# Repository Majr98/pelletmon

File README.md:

# WHAT AND WHY?

Our old boiler was previously connected to my IoT system. After replacing the boiler with a new one, we no longer have this option. So why not introduce it to a new boiler?

# THE TARGET

The goal of the project is to reverse engineer the CAN communication of the new boiler and expose real-time data to the IoT. By the way, the HC-SR04 sensor will measure the fuel level in the tank.

# DESIGN

The project will have its own PCB. Communication with the outside world will be carried out using ESP32 and fuel level measurement using HC-SR04. The SN65HVD230 chip will be used as the CAN transceiver. The software will be written in the Arduino environment in C ++ and will be powered with my IoT framework - ksIotFrameworkLib.

# KNOWN ISSUES

## HARDWARE

### rev 0.01a-0.01c
- GPIO0 is directly connected to SWITCH (S1), avoid setting direct HIGH state at that pin from software, because it can result in short circuit when pressing S1, as it will tie IO0 to ground directly.

## SOFTWARE
- <s>Hardcoded CAN support.</s> (now using VideNet, which is universal)
- <s>Sometimes at boot sends "zero" values to MQTT.</s>
- No support for fuel level sensor. (it was previously planned, but VideNet gives info about fuel usage)

# PICS

# Special thanks
- M-Works [ https://m-works.net/ ]
- Robert Labuz.

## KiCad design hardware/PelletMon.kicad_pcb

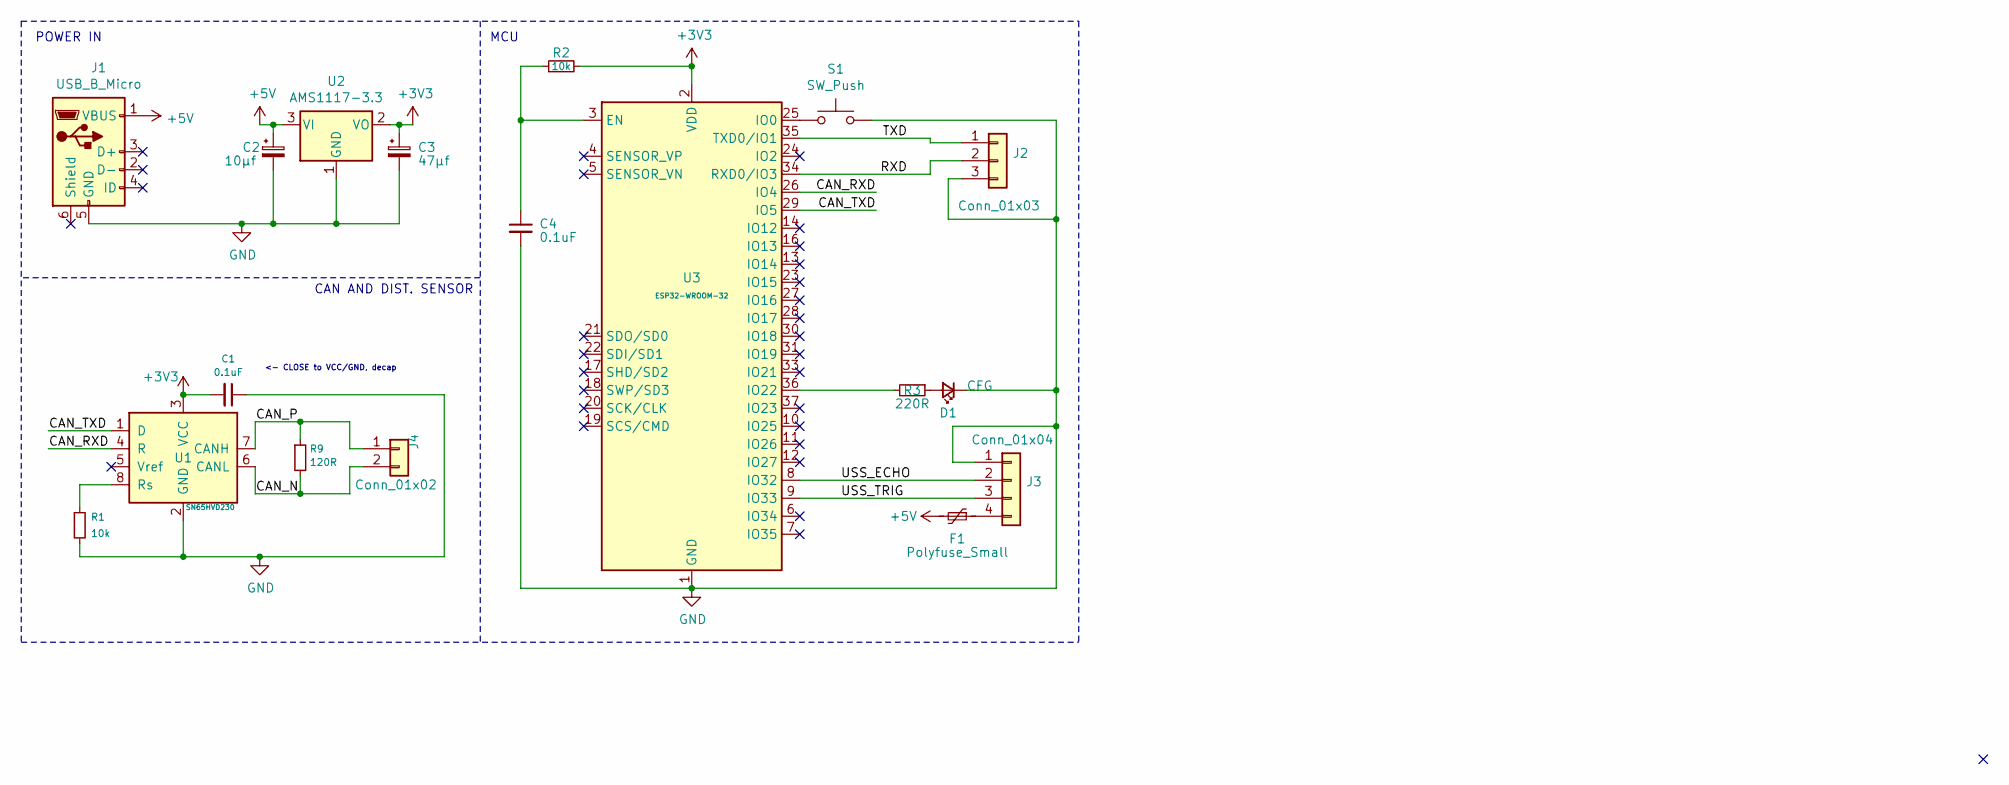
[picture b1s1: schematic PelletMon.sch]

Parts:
C1: 0.1uF; C_1206_3216Metric
C2: 10µf; CP_EIA-3216-10_Kemet-I; LCSC C126946
C3: 47µf; CP_EIA-3216-10_Kemet-I; LCSC C126946
C4: 0.1uF; C_1206_3216Metric; LCSC C126946
D1: CFG; LED_1206_3216Metric; LCSC C375459
F1: Polyfuse_Small; R_1206_3216Metric
J1: USB_B_Micro; USB_Micro-B_Molex-105017-0001; LCSC C132563
J2: Conn_01x03; PinHeader_1x03_P2.54mm_Vertical
J3: Conn_01x04; PinHeader_1x04_P2.54mm_Vertical
J4: Conn_01x02; PinHeader_1x02_P2.54mm_Vertical
R1: 10k; R_1206_3216Metric
R2: 10k; R_1206_3216Metric; LCSC C1489
R3: 220R; R_1206_3216Metric; LCSC C17948
R9: 120R; R_1206_3216Metric
S1: SW_Push; SW_SPST_B3SL-1022P
U1: SN65HVD230; SOIC-8_3.9x4.9mm_P1.27mm
U2: AMS1117-3.3; SOT-223-3_TabPin2; LCSC C6186
U3: ESP32-WROOM-32; ESP32-WROOM-32U

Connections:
+3V3: C1.2, C3.1, R2.2, U1.3 (VCC), U2.2 (VO), U3.2 (VDD)
+5V: C2.1, F1.2, J1.1 (VBUS), U2.3 (VI)
/CAN_N: J4.2, R9.2, U1.6 (CANL)
/CAN_P: J4.1, R9.1, U1.7 (CANH)
/CAN_RXD: U1.4 (R), U3.26 (IO4)
/CAN_TXD: U1.1 (D), U3.29 (IO5)
/RXD: J2.2, U3.34 (RXD0/IO3)
/TXD: J2.1, U3.35 (TXD0/IO1)
/USS_ECHO: J3.2, U3.8 (IO32)
/USS_TRIG: J3.3, U3.9 (IO33)
GND: C1.1, C2.2, C3.2, C4.2, D1.1 (K), J1.5 (GND), J2.3, J3.1, R1.2, S1.2, U1.2 (GND), U2.1 (GND), U3.1 (GND), U3.15 (GND), U3.38 (GND), U3.39 (GND)
unnamed: C4.1, R2.1, U3.3 (EN)
unnamed: D1.2 (A), R3.1
unnamed: F1.1, J3.4
unnamed: R1.1, U1.8 (Rs)
unnamed: R3.2, U3.36 (IO22)
unnamed: S1.1, U3.25 (IO0)

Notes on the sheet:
POWER IN
MCU
CAN AND DIST. SENSOR
<- CLOSE to VCC/GND, decap

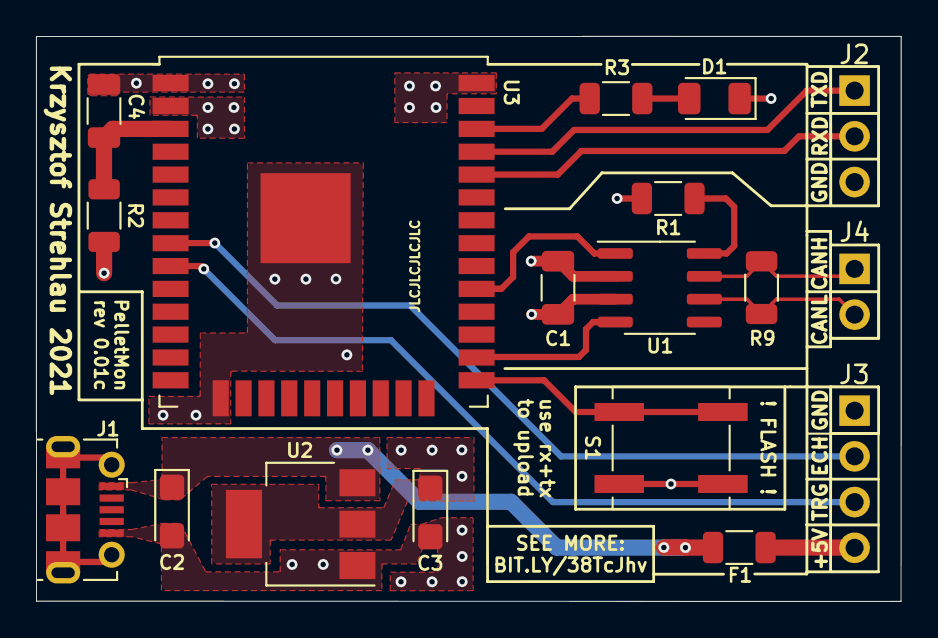
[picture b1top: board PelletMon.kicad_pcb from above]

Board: 4 copper layers, 48.0 x 31.4 mm, 18 parts (0 on the bottom side), 17 nets.

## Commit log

2021-01-06 Hardware design
2021-01-06 Update pcb
2021-01-06 Add renders
2021-01-07 PCB update
2021-01-07 Update gerbers and renders
2021-01-07 Last fixes before fab
2021-01-07 Before FAB
2021-01-07 Post fab - update renders
2021-01-12 Minor PCB tweaks
2021-01-12 Misc tweaks
2021-01-12 Update renders
2021-01-30 Firmware draft
2021-02-01 Cleaning up code
2021-02-01 Remove unused cpp
2021-02-01 Add readme draft to code
2021-02-01 Fix code readme
2021-02-01 Add sln
2021-02-01 Cleanup
2021-02-01 Bugfix
2021-02-01 Had some bugs, fixed them
2021-02-25 Fixes
2021-03-01 Small fix
2021-03-01 Tidy can
2021-03-04 Software tweaks
2021-03-06 Bulk send every 15s instead of send on change
2021-03-09 Add boiler2 temp, optimizations
2021-03-10 Handle CAN in interrupts
2021-03-10 Cleanups
2021-03-10 Atomic - keep in sync
2021-03-10 Fix compile error
2021-03-10 Refactor, code cleanup
2021-03-10 Remove canstats cmd
2021-03-13 Move critical functions to IRAM
2021-03-14 Small cleanups
2021-03-16 Fix typo
2021-03-18 Remove boiler2 temp
2021-03-18 Cleanup code
2021-04-19 Fix WDT
2021-04-19 Pics
2021-06-23 Hostname, chip temp, hasData tweaks
2021-06-24 Remove chip temp info
2021-07-06 New functions
2021-07-06 revert temp calc
2021-07-07 Refactoring of message handling
2021-07-07 add custom dbg commands
2021-07-08 Comments and code beautify
2021-07-08 Add basic remote control
2021-07-08 Add save settings
2021-07-11 Code beautify
2021-07-13 Refactor to support more videnet messages
2021-07-13 Small change
2021-07-16 Vide net changes
2021-07-16 Add Readme, License to solution.
2021-07-26 Add heating mode change support
2021-07-26 Fix missing queue handling
2021-07-26 Cleanup code - use lambdas as removeIf
2021-07-26 Clear requests by clear method
2021-07-27 Add burner usage, some code cleanup
2021-07-28 Remove CAN_IO module references, now everything is based on VideNet protocol
2021-07-28 VS project
2021-07-29 Misc fixes
2021-07-29 No interrupts when sending can message
2021-08-01 Move to better CAN driver
2021-08-01 Solution files
2021-08-02 Cleanups #2
2021-08-02 Tidy code
2021-08-08 Add can stop on init
2021-08-09 Switch to esp32_can and can_common
2021-09-04 Cleanup project
2021-09-04 Add new defs
2021-09-21 Add burner status
2021-09-22 Fix cpp warnings
2021-10-12 Return burner status as decimal
2021-10-12 Refresh state after change request
2021-11-03 Fix type, add failures
2021-11-03 Revert changes
2021-11-11 Config changes, remove vsarduino file (not required to be on git)
2021-11-12 Unifications
2021-11-29 Add error read
2021-11-30 Read alarm
2021-12-16 Change arduino core to run on cpu 0
2021-12-22 Code cleanup
2021-12-22 Fix readme
2021-12-24 Visual project filters
2021-12-26 Small cleanup
2021-12-27 Proper handling of vector (insert not mixed with erase in same iterator).
2021-12-27 Use temporary list to manage requests more efficient.
2021-12-28 Fix VideNetClient
2021-12-28 Tweak timed out request handling.
2021-12-28 Fix bad condition check.
2021-12-28 Remove external dependencies
2021-12-28 Fix SLN
2022-01-04 Update to support latest framework changes
2022-01-06 Fix controller enabled request, minor tweaks in uploadValuesToMqtt method.
2022-01-06 Remove unnecessary blink
2022-01-11 Request only controller state update on command.
2022-02-03 Comments, tweaks, etc.
2022-02-05 Use ksSafeListScopedSync to synchronize lists.
2022-02-05 Fix typo in VideNet.cpp
2022-02-05 Comments for scopedListSync
2022-02-06 Commments fix
2022-02-16 Add reset button support
2022-02-20 Imgs
2022-02-22 Reduce drive CAP on CAN RX/TX pins.
2022-02-23 Cosmetic changes
